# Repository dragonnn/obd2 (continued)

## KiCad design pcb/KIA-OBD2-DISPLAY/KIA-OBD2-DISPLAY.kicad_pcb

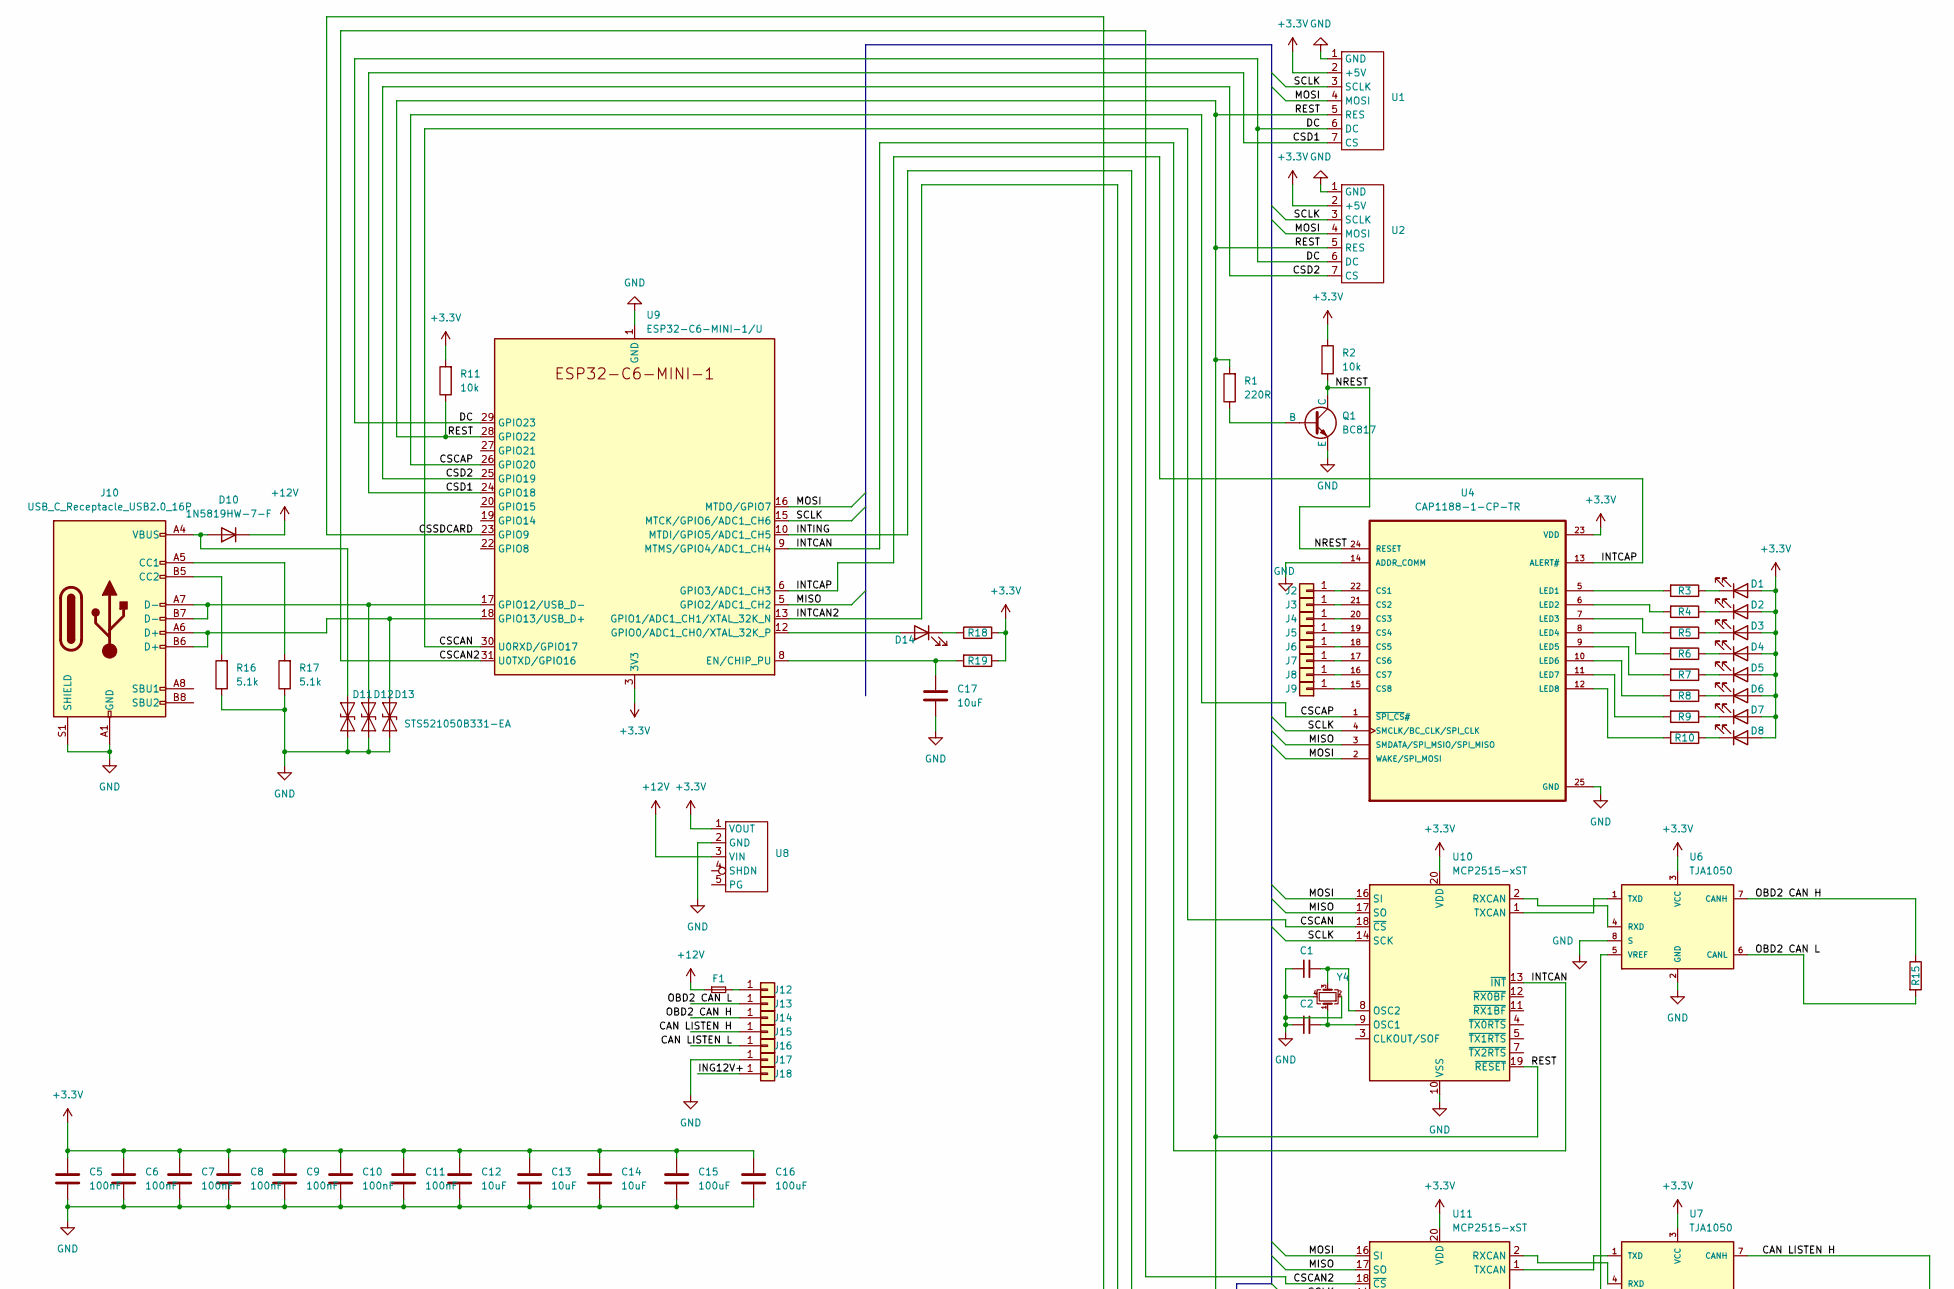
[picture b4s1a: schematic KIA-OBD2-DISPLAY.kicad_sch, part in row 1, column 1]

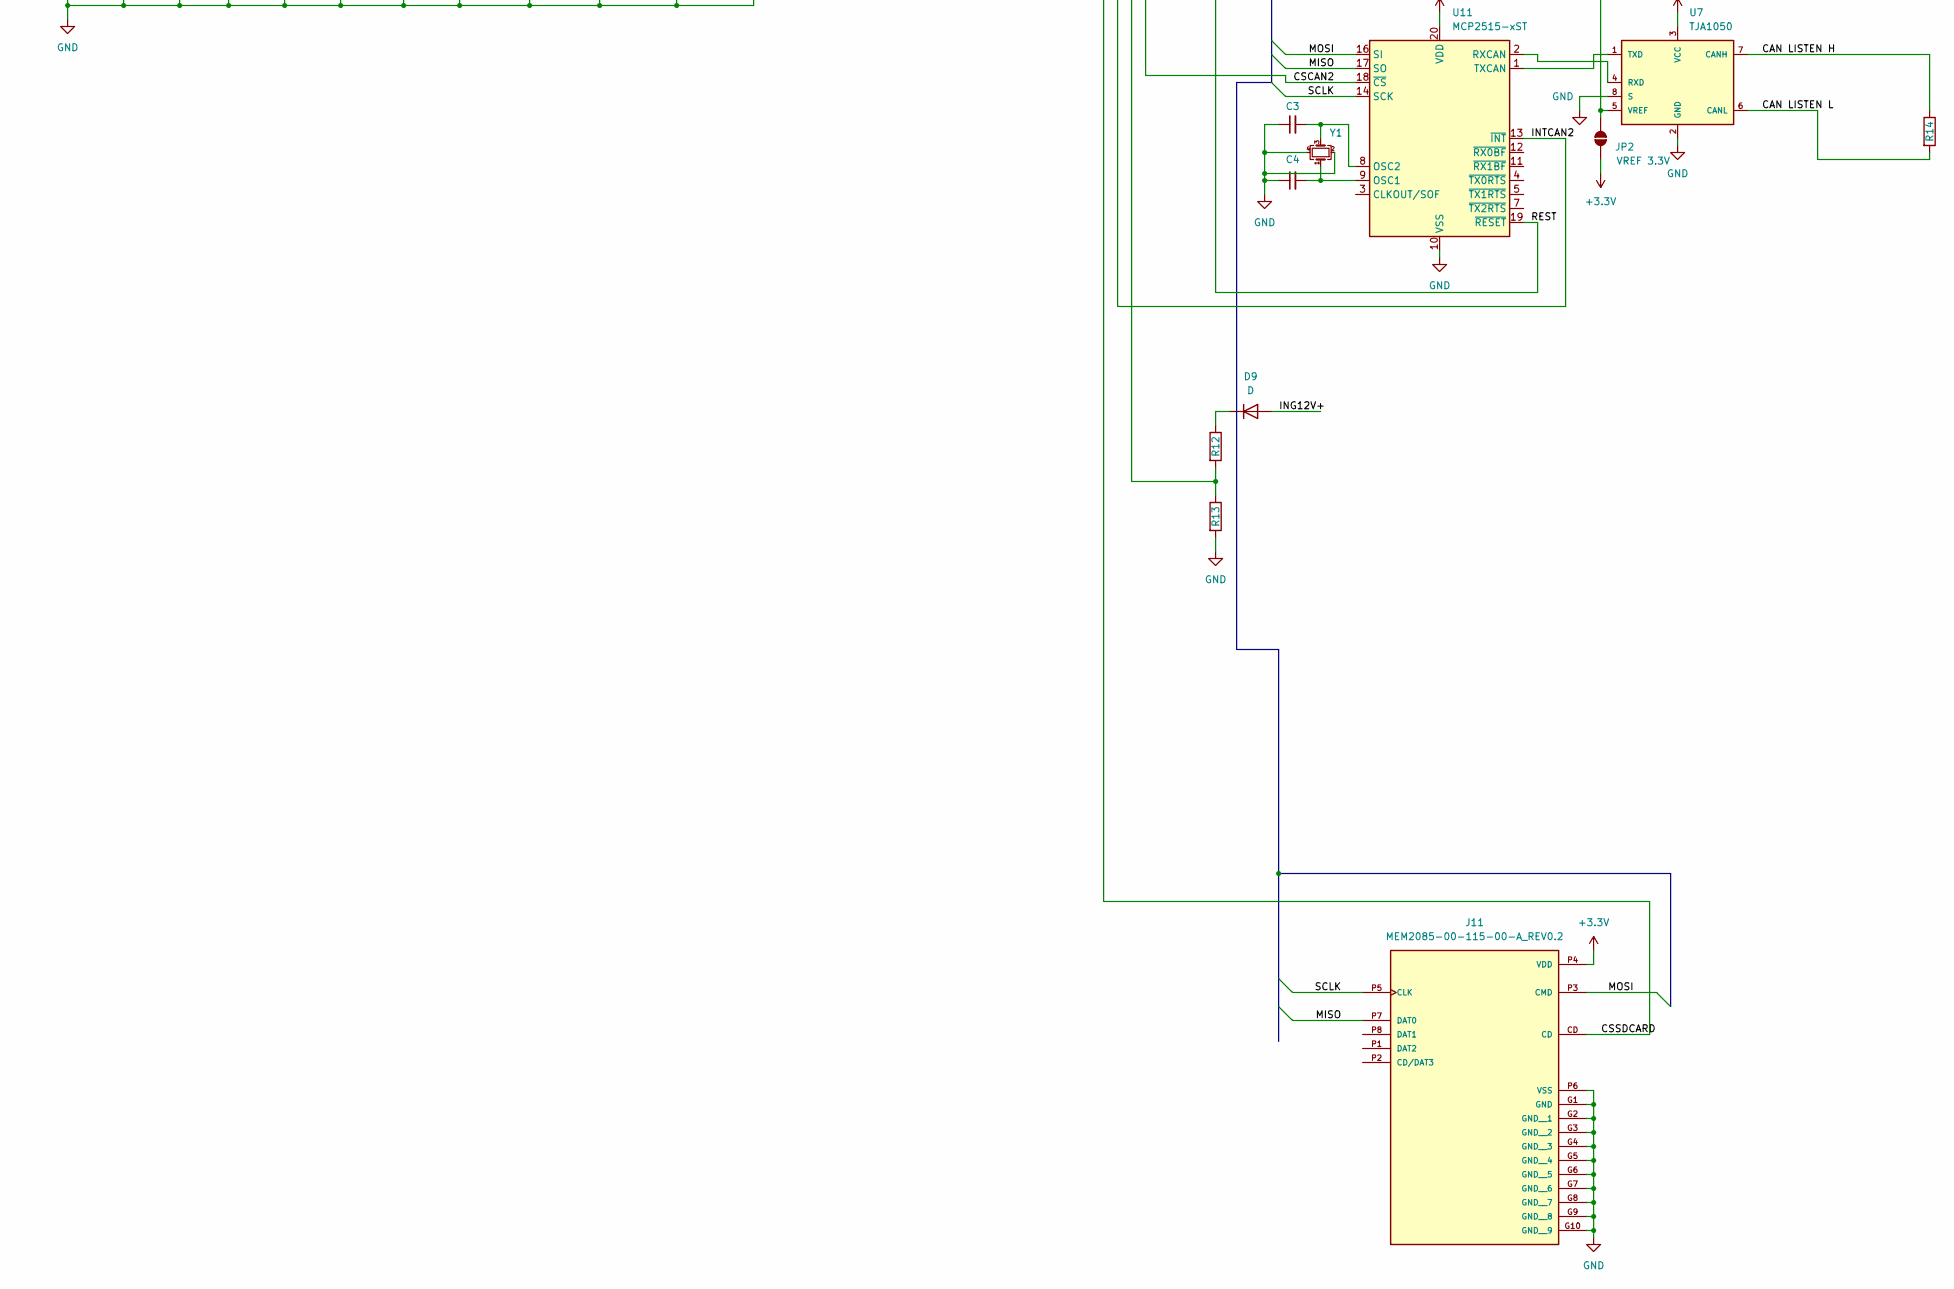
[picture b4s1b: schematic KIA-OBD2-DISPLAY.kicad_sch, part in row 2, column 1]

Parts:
C1, C2, C3, C4: 22pF; C_0805_2012Metric
C5, C6, C7, C8, C9, C10, C11: 100nF; C_0603_1608Metric
C12, C13, C14, C17: 10uF; C_0805_2012Metric
C15, C16: 100uF; C_1206_3216Metric
D1, D2, D3, D4, D5, D6, D7, D8, D14: LED; LED_QBLP617-IW
D9: D; D_0805_2012Metric
D10: 1N5819HW-7-F; D_SOD-123
D11, D12: SD05_SOD323; D_SOD-523
D13: STS521050B331-EA; D_SOD-523
F1: Fuse_Small; Fuseholder_Littelfuse_Nano2_154x
J2, J3, J4, J5, J6, J7, J8, J9: Conn_01x01; TestPoint_Pad_1.0x1.0mm
J10: USB_C_Receptacle_USB2.0_16P; USB_C_Receptacle_GCT_USB4085
J11: MEM2085-00-115-00-A_REV0.2; GCT_MEM2085-00-115-00-A_REV0.2; PARTREV 0.2
J12, J13, J14, J15, J16, J17, J18: Conn_01x01; TestPoint_THTPad_1.0x1.0mm_Drill0.5mm
JP2: VREF 3.3V; SolderJumper-2_P1.3mm_Open_RoundedPad1.0x1.5mm
Q1: BC817; SOT-323_SC-70
R1: 220R; R_0805_2012Metric
R2, R11, R19: 10k; R_0805_2012Metric
R3, R4, R5, R6, R7, R8, R9, R10, R18: 65R; R_0805_2012Metric
R12: 4.7k; R_0805_2012Metric
R13: 1k; R_0805_2012Metric
R14, R15: 120R; R_0805_2012Metric
R16, R17: 5.1k; R_0805_2012Metric
U1, U2: SH1122
U4: CAP1188-1-CP-TR; QFN50P400X400X90-25N; PARTREV 02-09-15
U6, U7: TJA1050; SOT96-1
U8: D24V10F3
U9: ESP32-C6-MINI-1/U; ESP32-C6-MINI-1
U10, U11: MCP2515-xST; TSSOP-20_4.4x6.5mm_P0.65mm
Y1, Y4: Crystal_GND24_Small; Crystal_SMD_3225-4Pin_3.2x2.5mm

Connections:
+3.3V: C5.1, C6.1, C7.1, C8.1, C9.1, C10.1, C11.1, C12.1, C13.1, C14.1, C15.1, C16.1, D1.2 (A), D2.2 (A), D3.2 (A), D4.2 (A), D5.2 (A), D6.2 (A), D7.2 (A), D8.2 (A), J11.P4 (VDD), JP2.1 (A), R2.1, R11.2, R18.2, R19.1, U1.2 (+5V), U2.2 (+5V), U4.23 (VDD), U6.3 (VCC), U7.3 (VCC), U8.1 (VOUT), U9.3 (3V3), U10.20 (VDD), U11.20 (VDD)
+12V: D10.1 (K), F1.1, U8.3 (VIN)
/CAN LISTEN H: J15.1, R14.1, U7.7 (CANH)
/CAN LISTEN L: J16.1, R14.2, U7.6 (CANL)
/CSCAN: U9.30 (U0RXD/GPIO17), U10.18 (~CS)
/CSCAN2: U9.31 (U0TXD/GPIO16), U11.18 (~CS)
/CSCAP: U4.1 (~SPI_CS#), U9.26 (GPIO20)
/CSD1: U1.7 (CS), U9.24 (GPIO18)
/CSD2: U2.7 (CS), U9.25 (GPIO19)
/CSSDCARD: J11.CD, U9.23 (GPIO9)
/DC: U1.6 (DC), U2.6 (DC), U9.29 (GPIO23)
/ING12V+: D9.2 (A), J18.1
/INTCAN: U9.9 (MTMS/GPIO4/ADC1_CH4), U10.13 (~INT)
/INTCAN2: U9.13 (GPIO1/ADC1_CH1/XTAL_32K_N), U11.13 (~INT)
/INTCAP: U4.13 (ALERT#), U9.6 (GPIO3/ADC1_CH3)
/INTING: R12.2, R13.1, U9.10 (MTDI/GPIO5/ADC1_CH5)
/MISO: J11.P7 (DAT0), U4.3 (SMDATA/SPI_MSIO/SPI_MISO), U9.5 (GPIO2/ADC1_CH2), U10.17 (SO), U11.17 (SO)
/MOSI: J11.P3 (CMD), U1.4 (MOSI), U2.4 (MOSI), U4.2 (WAKE/SPI_MOSI), U9.16 (MTDO/GPIO7), U10.16 (SI), U11.16 (SI)
/NREST: Q1.1 (C), R2.2, U4.24 (RESET)
/OBD2 CAN H: J14.1, R15.1, U6.7 (CANH)
/OBD2 CAN L: J13.1, R15.2, U6.6 (CANL)
/REST: R1.2, R11.1, U1.5 (RES), U2.5 (RES), U9.28 (GPIO22), U10.19 (~RESET), U11.19 (~RESET)
/SCLK: J11.P5 (CLK), U1.3 (SCLK), U2.3 (SCLK), U4.4 (SMCLK/BC_CLK/SPI_CLK), U9.15 (MTCK/GPIO6/ADC1_CH6), U10.14 (SCK), U11.14 (SCK)
GND: C1.1, C2.1, C3.1, C4.1, C5.2, C6.2, C7.2, C8.2, C9.2, C10.2, C11.2, C12.2, C13.2, C14.2, C15.2, C16.2, C17.2, D11.1 (A1), D12.1 (A1), D13.2 (A2), J10.A1 (GND), J10.A12 (GND), J10.B1 (GND), J10.B12 (GND), J10.S1 (SHIELD), J11.G1 (GND), J11.G2 (GND__1), J11.G3 (GND__2), J11.G4 (GND__3), J11.G5 (GND__4), J11.G6 (GND__5), J11.G7 (GND__6), J11.G8 (GND__7), J11.G9 (GND__8), J11.G10 (GND__9), J11.P6 (VSS), J17.1, Q1.3 (E), R13.2, R16.1, R17.1, U1.1 (GND), U2.1 (GND), U4.14 (ADDR_COMM), U4.25 (GND), U6.2 (GND), U6.8 (S), U7.2 (GND), U7.8 (S), U8.2 (GND), U9.1 (GND), U9.2 (GND), U9.11 (GND), U9.14 (GND), U9.36 (GND), U9.37 (GND), U9.38 (GND), U9.39 (GND), U9.40 (GND), U9.41 (GND), U9.42 (GND), U9.43 (GND), U9.44 (GND), U9.45 (GND), U9.46 (GND), U9.47 (GND), U9.48 (GND), U9.49 (GND), U9.50 (GND), U9.51 (GND), U9.52 (GND), U9.53 (GND), U10.10 (VSS), U11.10 (VSS), Y1.2, Y1.4, Y4.2, Y4.4
unnamed: D1.1 (K), R3.1
unnamed: D2.1 (K), R4.1
unnamed: D3.1 (K), R5.1
unnamed: D4.1 (K), R6.1
unnamed: D5.1 (K), R7.1
unnamed: D6.1 (K), R8.1
unnamed: D7.1 (K), R9.1
unnamed: D8.1 (K), R10.1
unnamed: D9.1 (K), R12.1
unnamed: D10.2 (A), D11.2 (A2), J10.A4 (VBUS), J10.A9 (VBUS), J10.B4 (VBUS), J10.B9 (VBUS)
unnamed: D12.2 (A2), J10.A7 (D-), J10.B7 (D-), U9.17 (GPIO12/USB_D-)
unnamed: D13.1 (A1), J10.A6 (D+), J10.B6 (D+), U9.18 (GPIO13/USB_D+)
unnamed: D14.2 (A), U9.12 (GPIO0/ADC1_CH0/XTAL_32K_P)
unnamed: D14.1 (K), R18.1
unnamed: J2.1, U4.22 (CS1)
unnamed: J3.1, U4.21 (CS2)
unnamed: J4.1, U4.20 (CS3)
unnamed: J5.1, U4.19 (CS4)
unnamed: J6.1, U4.18 (CS5)
unnamed: J7.1, U4.17 (CS6)
unnamed: J8.1, U4.16 (CS7)
unnamed: J9.1, U4.15 (CS8)
unnamed: J10.A5 (CC1), R17.2
unnamed: J10.B5 (CC2), R16.2
unnamed: F1.2, J12.1
unnamed: JP2.2 (B), U6.5 (VREF), U7.5 (VREF)
unnamed: Q1.2 (B), R1.1
unnamed: R3.2, U4.5 (LED1)
unnamed: R4.2, U4.6 (LED2)
unnamed: R5.2, U4.7 (LED3)
unnamed: R6.2, U4.8 (LED4)
unnamed: R7.2, U4.9 (LED5)
unnamed: R8.2, U4.10 (LED6)
unnamed: R9.2, U4.11 (LED7)
unnamed: R10.2, U4.12 (LED8)
unnamed: C17.1, R19.2, U9.8 (EN/CHIP_PU)
unnamed: C2.2, U10.9 (OSC1), Y4.1
unnamed: C1.2, U10.8 (OSC2), Y4.3
unnamed: U6.4 (RXD), U10.2 (RXCAN)
unnamed: U6.1 (TXD), U10.1 (TXCAN)
unnamed: C4.2, U11.9 (OSC1), Y1.1
unnamed: C3.2, U11.8 (OSC2), Y1.3
unnamed: U7.4 (RXD), U11.2 (RXCAN)
unnamed: U7.1 (TXD), U11.1 (TXCAN)

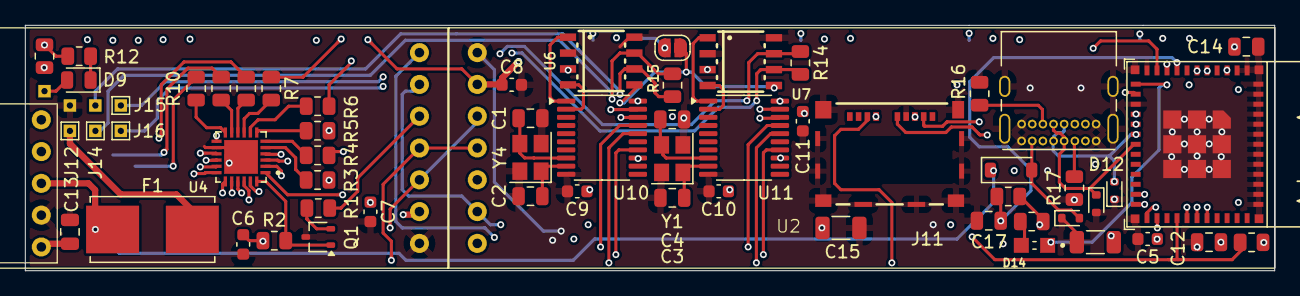
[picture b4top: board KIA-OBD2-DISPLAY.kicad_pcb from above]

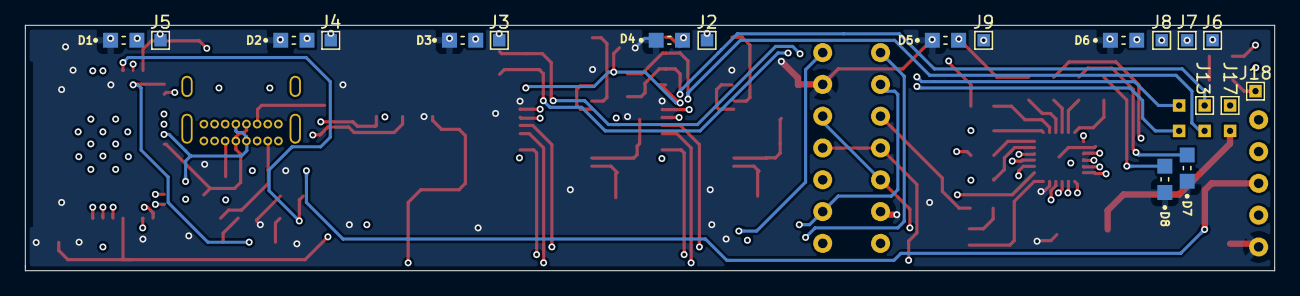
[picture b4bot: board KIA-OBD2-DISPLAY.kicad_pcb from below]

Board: 4 copper layers, 99.8 x 19.6 mm, 81 parts (19 on the bottom side), 68 nets.

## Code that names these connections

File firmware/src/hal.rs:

use defmt::{info, unwrap};
//use defmt_rtt as _;
use display_interface_spi::SPIInterface;
use embassy_embedded_hal::shared_bus::asynch::spi::{SpiDevice, SpiDeviceWithConfig};
use embassy_sync::{blocking_mutex::raw::CriticalSectionRawMutex, mutex::Mutex};
use esp_backtrace as _;
use esp_hal::{
    aes::dma::AesDma,
    clock::Clocks,
    delay::Delay,
    dma::{Dma, DmaChannel0, DmaPriority, DmaRxBuf, DmaTxBuf},
    dma_buffers, dma_descriptors,
    gpio::{Input, Io, Output, Pull},
    peripherals::Peripherals,
    prelude::*,
    rtc_cntl::Rtc,
    spi::{
        master::{Spi, SpiDmaBus},
        FullDuplexMode, SpiMode,
    },
    timer::{timg::TimerGroup, OneShotTimer},
    usb_serial_jtag::UsbSerialJtag,
    Async,
};
use esp_ieee802154::{Config, Frame, Ieee802154};
use sh1122::{display::DisplayRotation, AsyncDisplay, PixelCoord};
use static_cell::StaticCell;

use crate::{cap1188::Cap1188, mcp2515::Mcp2515, obd2, power, types};

defmt::timestamp!("{=u32:us}", { embassy_time::Instant::from_ticks(0).elapsed().as_micros() as u32 });

pub struct Hal {
    pub display1: types::Display1,
    pub display2: types::Display2,
    pub buttons: types::Cap1188,
    pub obd2: obd2::Obd2,
    #[cfg(feature = "usb_serial")]
    pub usb_serial: types::UsbSerial,
    pub power: power::Power,
    pub led: types::Led,
    pub ieee802154: Ieee802154<'static>,
}

macro_rules! mk_static {
    ($t:ty,$val:expr) => {{
        static STATIC_CELL: static_cell::StaticCell<$t> = static_cell::StaticCell::new();
        #[deny(unused_attributes)]
        let x = STATIC_CELL.uninit().write(($val));
        x
    }};
}

pub struct SpiBus {
    spi: SpiDmaBus<'static, esp_hal::peripherals::SPI2, FullDuplexMode, Async>,
}

impl SpiBus {
    pub fn new(spi: SpiDmaBus<'static, esp_hal::peripherals::SPI2, FullDuplexMode, Async>) -> Self {
        Self { spi }
    }
}

impl embedded_hal_async::spi::ErrorType for SpiBus {
    type Error = esp_hal::spi::Error;
}

impl embedded_hal_async::spi::SpiBus for SpiBus {
    async fn read(&mut self, words: &mut [u8]) -> Result<(), Self::Error> {
        self.spi.read_async(words).await
    }

    async fn write(&mut self, words: &[u8]) -> Result<(), Self::Error> {
        self.spi.write_async(words).await
    }

    async fn transfer(&mut self, read: &mut [u8], write: &[u8]) -> Result<(), Self::Error> {
        self.spi.transfer_async(read, write).await
    }

    async fn transfer_in_place(&mut self, words: &mut [u8]) -> Result<(), Self::Error> {
        self.spi.transfer_in_place_async(words).await
    }

    async fn flush(&mut self) -> Result<(), Self::Error> {
        //self.spi.flush_async().await
        Ok(())
    }
}

impl embassy_embedded_hal::SetConfig for SpiBus {
    type Config = u32;

    type ConfigError = ();

    fn set_config(&mut self, config: &Self::Config) -> Result<(), Self::ConfigError> {
        self.spi.change_bus_frequency(config.MHz());
        Ok(())
    }
}

pub fn init() -> Hal {
    let mut config = esp_hal::Config::default();
    config.cpu_clock = CpuClock::max();
    let peripherals = esp_hal::init(config);
    //let system = SystemControl::new(peripherals.SYSTEM);
    //let clocks = ClockControl::max(system.clock_control).freeze();
    let delay = Delay::new();
    delay.delay_micros(100u32);

    let timg0 = TimerGroup::new(peripherals.TIMG0);

    esp_hal_embassy::init(timg0.timer0);
    let io = Io::new(peripherals.GPIO, peripherals.IO_MUX);
    let rtc = Rtc::new(peripherals.LPWR);

    let dma = Dma::new(peripherals.DMA);
    let dma_channel = dma.channel0;

    let sclk = io.pins.gpio6;
    let mosi = io.pins.gpio7;
    let miso = io.pins.gpio2;

    let (rx_buffer, rx_descriptors, tx_buffer, tx_descriptors) = dma_buffers!(32000);
    let dma_rx_buf = unwrap!(DmaRxBuf::new(rx_descriptors, rx_buffer).ok());
    let dma_tx_buf = unwrap!(DmaTxBuf::new(tx_descriptors, tx_buffer).ok());

    let spi = Spi::new(peripherals.SPI2, 6.MHz(), SpiMode::Mode0)
        .with_sck(sclk)
        .with_mosi(mosi)
        .with_miso(miso)
        .with_dma(dma_channel.configure_for_async(false, DmaPriority::Priority0))
        .with_buffers(dma_rx_buf, dma_tx_buf);

    let mut dc = Output::new(io.pins.gpio23, false.into());
    let mut cs_display1 = Output::new(io.pins.gpio18, false.into());
    let mut cs_display2 = Output::new(io.pins.gpio19, false.into());
    let mut cs_cap1188 = Output::new(io.pins.gpio20, false.into());
    let mut cs_mcp2515 = Output::new(io.pins.gpio17, false.into());
    let int_mcp2515 = Input::new(io.pins.gpio4, Pull::Up);
    let mut rs = Output::new(io.pins.gpio22, true.into());
    let ing = Input::new(io.pins.gpio5, Pull::Up);
    let int_cap1188 = Input::new(io.pins.gpio3, Pull::Up);
    let led = Output::new(io.pins.gpio0, false.into());

    dc.set_high();
    rs.set_low();
    cs_display1.set_high();
    cs_display2.set_high();
    cs_cap1188.set_high();
    cs_mcp2515.set_high();
    delay.delay_micros(2u32);
    rs.set_high();

    delay.delay_micros(2u32);

    rs.set_low();
    delay.delay_micros(2u32);
    rs.set_high();
    delay.delay_micros(2u32);

    let dc2 = unsafe { core::ptr::read(&dc) };

    static SPI_BUS: StaticCell<Mutex<CriticalSectionRawMutex, SpiBus>> = StaticCell::new();
    let spi_bus = SPI_BUS.init(Mutex::new(SpiBus::new(spi)));

    let display1_spi = SpiDeviceWithConfig::new(spi_bus, cs_display1, 20);
    let display2_spi = SpiDeviceWithConfig::new(spi_bus, cs_display2, 20);
    let cap1188_spi = SpiDeviceWithConfig::new(spi_bus, cs_cap1188, 5);
    let mcp2515_spi = SpiDeviceWithConfig::new(spi_bus, cs_mcp2515, 10);
    let interface1 = SPIInterface::new(display1_spi, dc);
    let interface2 = SPIInterface::new(display2_spi, dc2);

    let display1 = AsyncDisplay::new(interface1, PixelCoord(256, 64), PixelCoord(0, 0), DisplayRotation::Rotate180)
        .into_buffered_graphics_mode();

    let display2 = AsyncDisplay::new(interface2, PixelCoord(256, 64), PixelCoord(0, 0), DisplayRotation::Rotate0)
        .into_buffered_graphics_mode();

    let cap1188 = Cap1188::new(cap1188_spi, int_cap1188);
    let mcp2515 = Mcp2515::new(mcp2515_spi, int_mcp2515);

    #[cfg(feature = "usb_serial")]
    let usb_serial = UsbSerialJtag::new_async(peripherals.USB_DEVICE);

    info!("HAL initialized");

    let ieee802154 = Ieee802154::new(peripherals.IEEE802154, peripherals.RADIO_CLK);

    Hal {
        display1,
        display2,
        buttons: cap1188,
        obd2: obd2::Obd2::new(mcp2515),
        #[cfg(feature = "usb_serial")]
        usb_serial,
        power: power::Power::new(ing, delay, rtc, rs),
        led,
        ieee802154,
    }
}

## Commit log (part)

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2024-10-18 prepare lte modem uarte read
2024-10-18 prepare uarte receive
2024-10-18 prepare uarte receiving
2024-10-23 add lte-modem reset manager
2024-10-23 disable link with async
2024-10-23 refresh gnss less on battery under 50
2024-10-29 prepare event bus rework
2024-10-29 prepare serde encrypt shared key key
2024-10-29 prepare iee802154 send ticker
2024-10-29 prepare frame sending
2024-10-30 prepare ieee802154 packet spliting
2024-10-30 prepare chunk gathering
2024-11-01 lte-modem decrypt recv
2024-11-01 prepare dtls sending data
2024-11-03 frame sending and reciving
2024-11-03 use postcard with crc
2024-11-04 rework sending data to ha-daemon
2024-11-05 basic working ha-daemon connect
2024-11-05 more ha-daemon work
2024-11-05 improve ieee802154 bridge recovery
2024-11-05 add TxMessage id and timestamp
2024-11-05 add on board charger frame
2024-11-05 start working on charging tracking
2024-11-05 adjust dashboard power off
2024-11-06 improve bridge robustness
2024-11-06 remove entry from hashmap before insert
2024-11-06 save last value in simple json to allow resending to ha during register sensor
2024-11-06 add obd2 pid sets
2024-11-06 first icu frame
2024-11-06 more icu pids
2024-11-06 add more ha-daemon variables
2024-11-06 go to ignition_off if detected
2024-11-07 add esp-backtrace panic restart
2024-11-07 add more robust ignition state handling
2024-11-08 change location of enabling/disabling Lcd screen
2024-11-10 add icu1smk pid frame
2024-11-10 send gnss state over link
2024-11-10 add battery state into modem type
2024-11-10 remove comment code
2024-11-10 get modem battery state on connect
2024-11-10 add extra state ieee802154 frame sending
2024-11-10 adjust main dashboard state logic
2024-11-10 add modem_gnss_state update
2024-11-10 don't print config on boot
2024-11-10 add serializer with round down to ha state
2024-11-10 log gnss state to ha
2024-11-10 disable log
2024-11-10 shutdown add delay before sending request
2024-11-11 add touch pcb
2024-11-11 add info about odb2 loop all pid readed
2024-11-11 handle deep sleep esp better
2024-11-13 store pids in a mutex instead of channel to avoid missing sending values
2024-11-13 add new values to ha
2024-11-13 don't send gnss state when link is not connected
2024-11-13 reset pid mutex right after cloning
2024-11-15 use ip address from env
2024-11-18 prepare modem ack
2024-11-19 prepare RxFrames
2024-11-19 send RxMessages to obd2-dashboard
2024-11-21 add modem reset command
2024-11-21 switch to publish_immediate
2024-11-21 resend messages on no ack
2024-11-22 add error types to ha ws
2024-11-23 add icu3 pid
2024-11-23 add pid errors
2024-11-23 improve gnss fix
2024-11-24 allow reciving rxframes on odb2-dashboard
2024-11-24 searching for skiping first transmit bug
2024-11-25 improve ieee802154 connection
2024-11-25 rework types message ids
2024-11-25 add sleep after sending messages in bridge
2024-11-26 rework obd2-dashboard ieee802154 sending and receving
2024-11-26 esp-hal update
2024-11-27 fix wrong pin on int_mcp2515_2
2024-11-27 fix ieee802154 support
2024-11-30 improve battery usage of modem and shutdown states
2024-11-30 rework modem charging control
2024-11-30 improve sms sending
2024-12-01 improve gnss state
2024-12-02 improve i2c reset on nrf
2024-12-02 track i2c errors per device
2024-12-02 fix default address for reseting at init
2024-12-02 add modem restart reasons
2024-12-02 improve gnss idle time
2024-12-02 reset reason tracking
2024-12-05 improve modem state handling
2024-12-05 clear low capacity charging
2024-12-05 more low_capacity_forced_charging clearing
2024-12-07 use thing91 button to reset uarte
2024-12-10 rework gnss to use external module
2024-12-11 remove last modem fix checking in obd2 dashboard
2024-12-11 fix external gnss fix processing
2024-12-11 when obd2 set is none do not report all success read
2024-12-16 obd2 errors debug
2024-12-16 last gps comunication
2024-12-16 initialize buttons always
2024-12-16 debug battery state on lte modem
2024-12-17 add enable/disable charging in adp5360
2024-12-17 do not disable charging if CheckCharging state
2024-12-20 improve gnss handling
2025-01-21 deps update
2025-02-02 panic debug
2025-02-03 modem spm update
2025-02-03 nrf-modem from crates.io
2025-02-03 toolchain update
2025-02-03 tinyrlibc
2025-02-03 fix lte-modem target
2025-02-03 disable defmt brtt
2025-02-03 log hard fault
2025-03-02 fix pids length checking
2025-03-02 rework system init
2025-03-03 add timeout on can_listen shutdown
2025-03-03 disable checking for debugger
2025-03-03 improve mcp2515 init
2025-03-04 remove obd2 init spi lock
2025-03-05 More robust spi init
2025-03-05 remove can_listen spi lock
2025-03-05 remove debugger check
2025-03-05 send shutdown message on init
2025-03-05 add usb-serial jtag defmt
2025-03-05 sh1122 fixes
2025-03-05 ieee802154disable defmt
2025-03-05 improve defmt logging and mcp2515 init
2025-03-06 improve obd2 timeout
2025-03-06 add esp temp monitoring
2025-03-06 add custom obd2 frame command to types
2025-03-06 more robust system init and change sms timeout
2025-03-07 add obd2 init checks
2025-03-07 more obd2 init stuff
2025-03-09 improve obd2 init
2025-03-24 fix display init
2025-03-24 recalibrate cap buttons
2025-03-24 button debug
2025-03-24 add obd2 custom frame sending
2025-03-24 adjust buttons on touch
2025-03-24 fix alloc
2025-03-27 add custom frame sending from cli
2025-03-27 add project license
2025-03-28 enable spm flashing
2025-03-28 disable zephyr.bin
2025-03-30 use zephyr.bin for spm
2025-03-30 use nrf9160 in secure mode
2025-03-31 debuging nrf9160 non secure mode
2025-03-31 spelling
2025-03-31 restore working lte-modem
2025-03-31 enable light sensor
2025-04-01 reset uarte on boot always
2025-04-01 box vec
2025-04-01 fix spm
2025-04-01 fix charging init
2025-04-12 adjust buttons
2025-04-22 remove widget positions
2025-04-22 add connection icons
2025-04-22 more fixes for obd2 behaviour
2025-04-27 remote debug
2025-04-27 working ac pid decode, and more similator stuff
2025-04-27 replace f64 with f32 to safe on udp transmit size
2025-04-27 more f32 work
2025-04-27 more f32 fixes
2025-04-27 add ac compress icon
2025-04-27 improve obd handling
2025-04-27 add sms close/open event
2025-04-27 improve iee802154
2025-04-27 add simulator
2025-04-27 add draft for display simulator
2025-04-29 update setting last_receive/last_send in callbacks
2025-04-29 split similator into server and ui
2025-05-03 prepare display emulator server
2025-05-03 working obd2 display simulator
2025-05-03 adjust ui
2025-05-03 fix rust analyzer in obd2 display simulator server
2025-05-03 improve simulator ui
2025-05-04 decode transaxel pid
2025-05-04 fix fuel rate rendering
2025-05-04 add transaxle temp display
2025-05-04 add humidity and ac icon
2025-05-04 adjust transaxel temps bytes
2025-05-04 draw position after humidity
2025-05-08 improve humidity icon
2025-05-30 more sms fixes
2025-06-15 modem deps update
2025-07-13 rework sms handling
2025-07-13 add quick sms send
2025-07-13 fix timeout in sms task
2025-07-14 adjust sms building
2025-07-17 fix sms insert
2025-07-21 logic adjust
2025-07-21 timeout adjust
2025-07-22 display init rework
2025-07-22 sms task timeout
2025-08-08 move to upstream statig
2025-08-08 prepare charging display
2025-08-08 prepare testing charging screen
2025-08-08 prepare on board charger widget
2025-08-08 finish charging screen
2025-08-08 major adjustments to charging screen
2025-08-12 fix rendering charging state
2025-08-12 adjust sms send timeout
2025-08-12 fix sms
2025-08-14 fix missing go to charging display in lcd linit
2025-08-14 add draw in charging on each Obd2Event
2025-09-02 add xiao testing board
2025-09-21 state changes
2025-09-21 improve charging state
2025-09-28 lte-modem deps update
2025-09-28 more deps update
2025-09-28 improve sms logic
2025-09-28 esp-hal 1.0.0
2025-09-28 fix server simulator
2025-09-28 fix xiao board
2025-09-28 fix spi bus speed
2025-11-11 lte modem display blink
2025-11-11 cleanup logs, enable modem stats task
2025-12-28 add lte-modem ssd1306 display
2025-12-28 fix battery refresh in display
2025-12-28 fix spi speed
2025-12-29 always push gnss fix to internal channel
2025-12-29 extract dbm refresh to a dedicated task
2025-12-29 embassy-nrf 0.9
2026-03-29 improve shutdown state handling
2026-04-06 prepare sms send replace
2026-04-06 modem use send message instead of send_sms
2026-04-06 put modem message into ha
2026-04-08 ack debug
2026-04-08 improve obd2 reading
2026-04-08 filter obd2 ids
2026-04-09 fix lock
2026-04-09 improve arrow rendering
2026-04-10 optimize render
2026-04-10 debug
2026-04-11 widget time debug
2026-04-11 more arrow work
2026-04-11 arrow fixing
2026-04-11 add arrow rendering logs
2026-04-11 better arrow logs
2026-04-11 formating
2026-04-11 Revert "better arrow logs"
    This reverts commit 7ed5d9eaae50796730436a32e26790b3956f759b.
2026-04-11 adjust arrow rendering
2026-04-11 simplfy arrow rendering
2026-04-11 optimize arrow rendering
2026-04-11 fixed arrow rendering
2026-04-11 universal rendering fix
2026-04-11 adjust arrow speed
2026-04-11 adjust arrow width to fix edges
2026-04-11 more arrow adjust
2026-04-11 fix aarrow color
2026-04-12 full deps update
2026-04-12 power pin debounce
2026-04-12 revert debouncing
2026-04-13 fix up logs
2026-04-13 improve obd2 timeouts
2026-04-13 fix wakeup pin
2026-04-13 better debug
2026-04-13 fix ing_pin on xaio
2026-04-13 more power and xaio test board fixes
2026-04-14 panic fix
2026-04-14 TransaxlePid length check
2026-04-14 improve last ignition on handling
2026-04-14 fix last ignition on handling
2026-04-14 fix shutdown duration
2026-04-14 probe-rs patch
2026-04-14 heap use dram2 and fix memory.x
2026-04-14 max shutdown attempts
2026-04-14 max init attempts
2026-04-15 shutdown debug
2026-04-24 more clean up
2026-04-24 fix going into deep sleep
2026-04-24 sleep fixes
2026-04-24 ac pid period
2026-04-24 improve obd2 timing
